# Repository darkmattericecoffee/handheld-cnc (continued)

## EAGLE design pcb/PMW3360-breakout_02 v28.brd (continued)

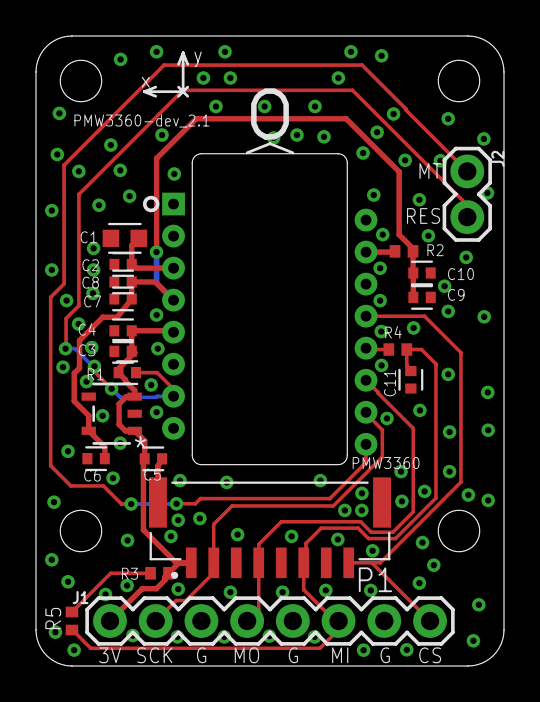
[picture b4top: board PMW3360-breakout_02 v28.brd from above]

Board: 2 copper layers, 26.0 x 35.0 mm, 21 parts (0 on the bottom side), 13 nets.

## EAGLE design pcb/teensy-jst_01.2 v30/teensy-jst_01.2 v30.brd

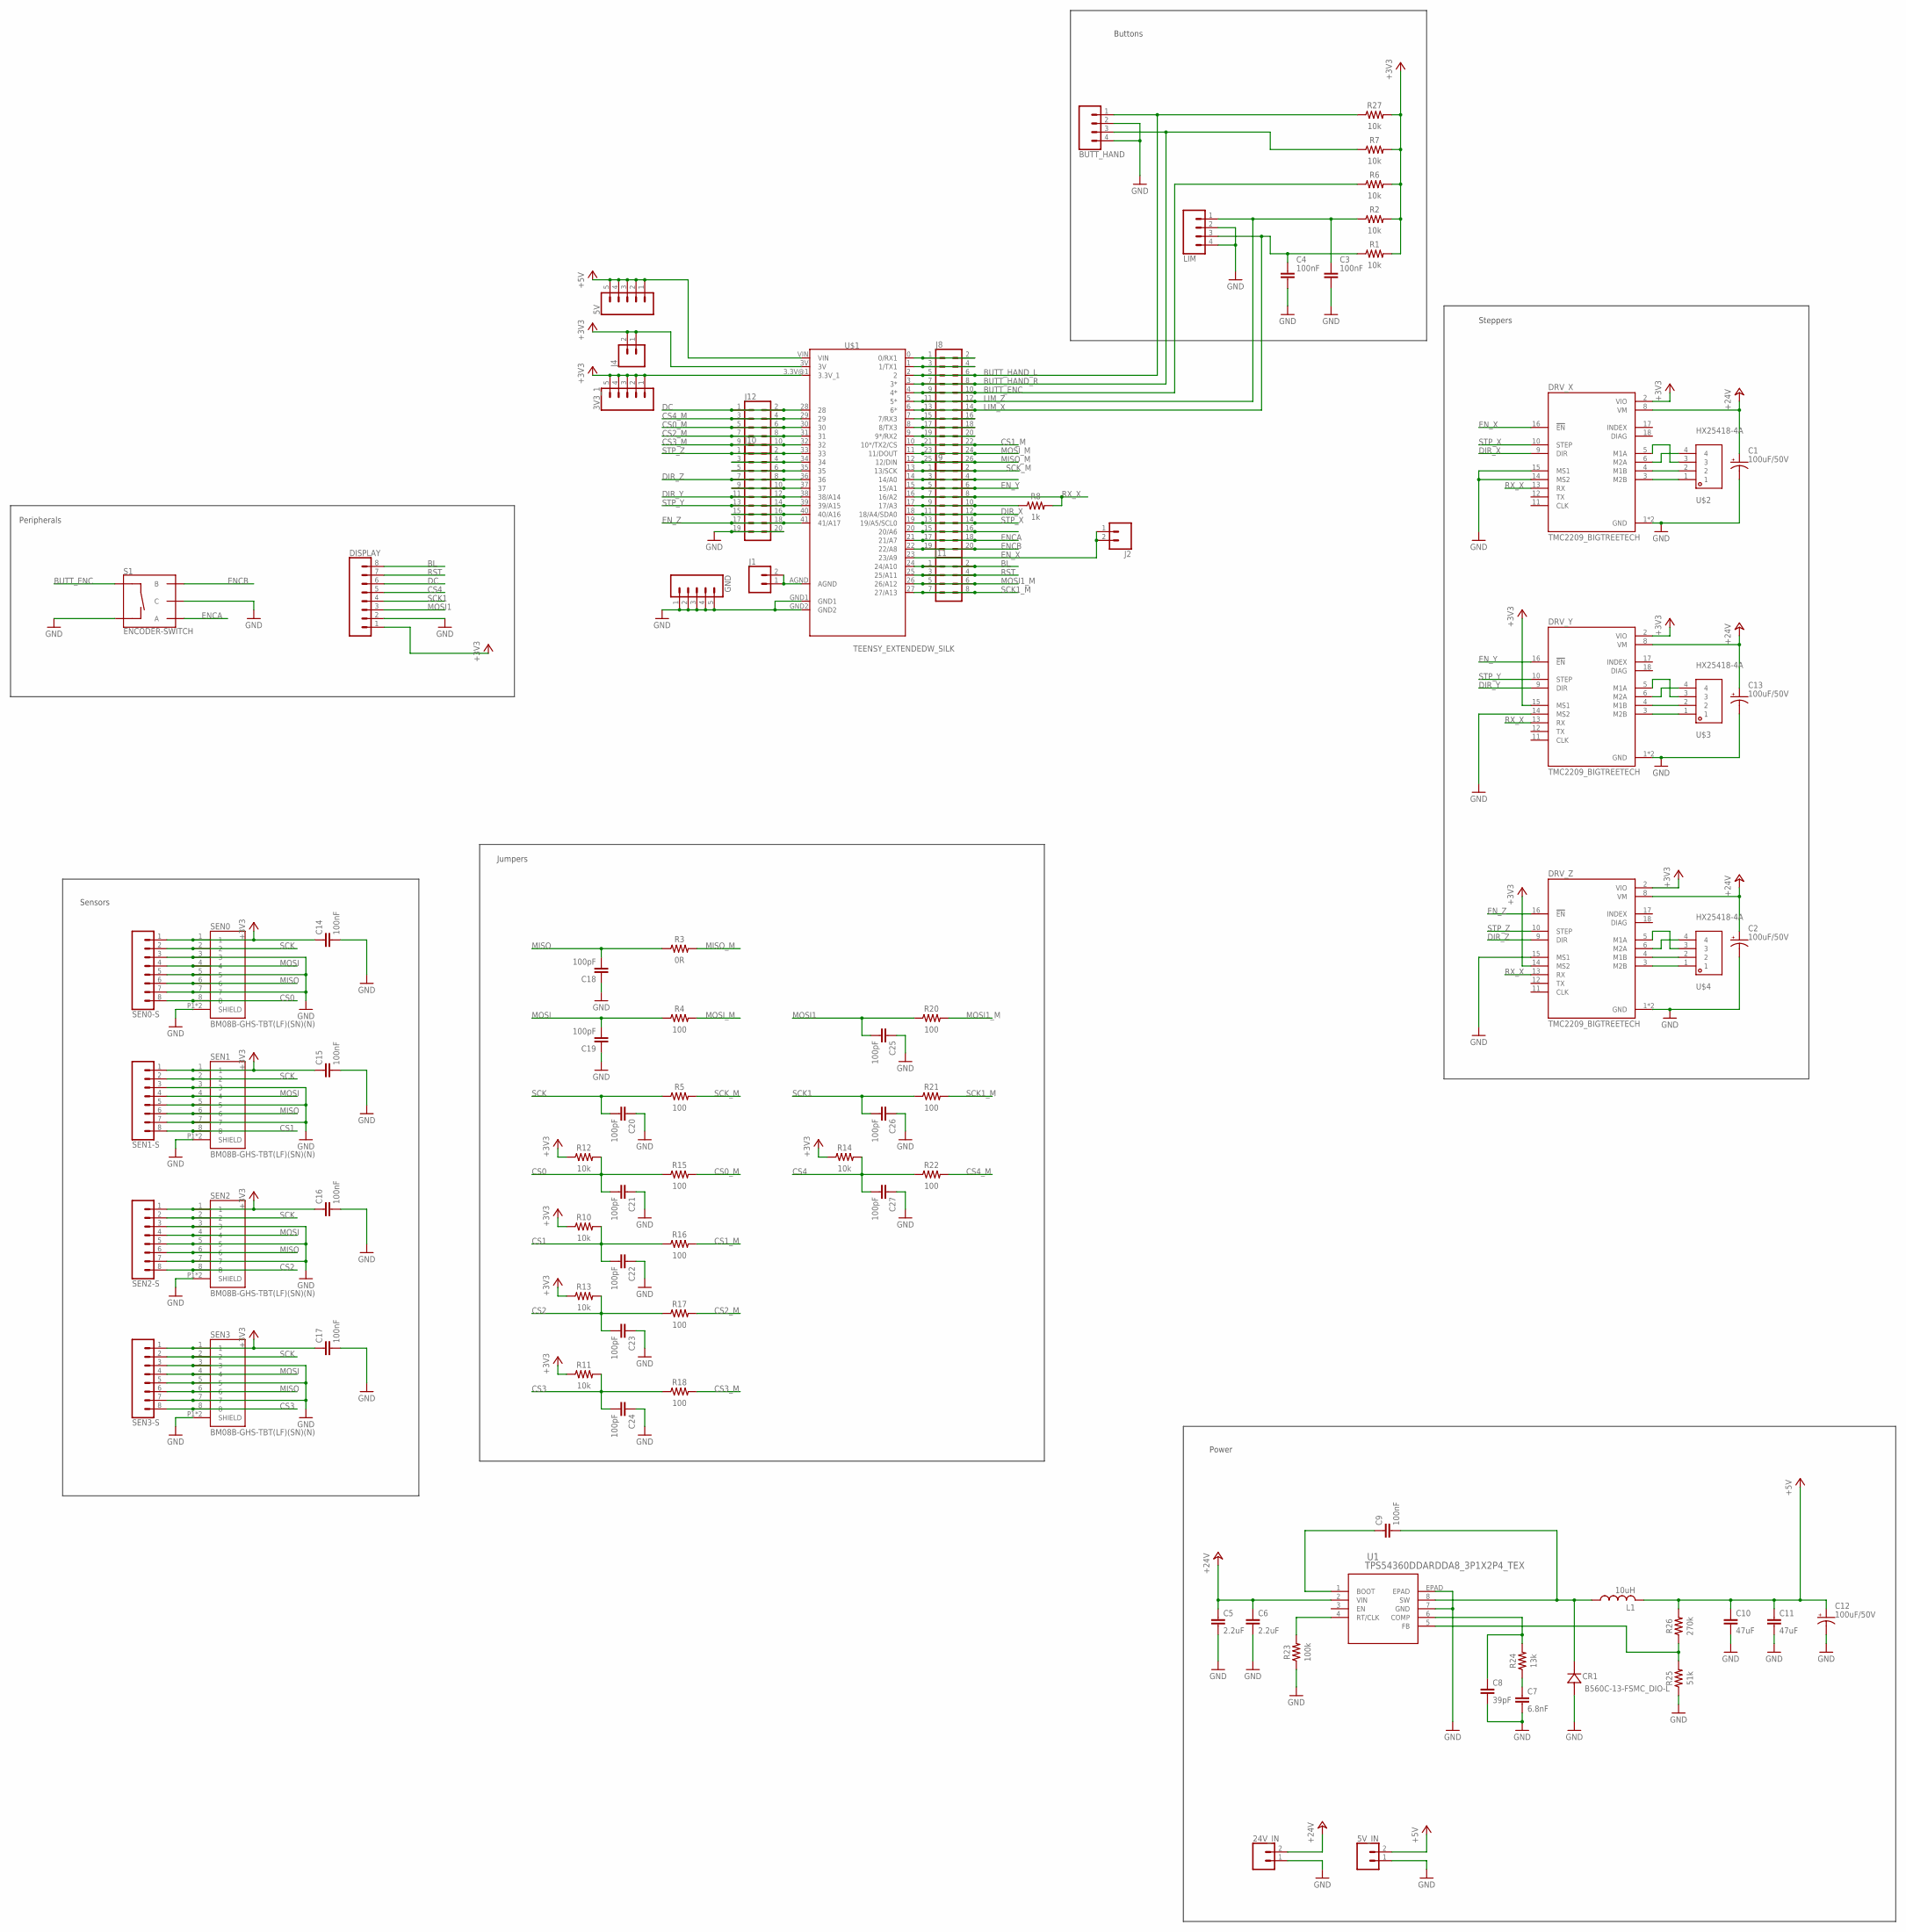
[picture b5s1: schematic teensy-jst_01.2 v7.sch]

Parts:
3V3_1, 5V: CONN_05PTH; 1X05
5V_IN, 24V_IN: CONN_025MM; SCREWTERMINAL-5MM-2
BUTT_HAND: CONN_041X04_NO_SILK; 1X04_NO_SILK
C1, C2, C12, C13: 100uF/50V; PANASONIC_D
C3, C4: 100nF; C0603
C5, C6: 2.2uF; C0603
C7: 6.8nF; C0402
C8: 39pF; C0402
C9, C14, C15, C16, C17: 100nF; C0402
C10, C11: 47uF; C0603
C18, C19, C20, C21, C23, C24, C25, C26, C27: 100pF; C0402K
C22: 100pF; C0402
CR1: B560C-13-FSMC_DIO-L; SMC_DIO-L
DISPLAY: CONN_08"; 1X08
DRV_X: TMC2209_BIGTREETECH; MODULE_TMC2209_BIGTREETECH
DRV_Y: TMC2209_BIGTREETECH; MODULE_TMC2209_BIGTREETECH
DRV_Z: TMC2209_BIGTREETECH; MODULE_TMC2209_BIGTREETECH
GND: CONN_05PTH; 1X05
J1, J2, J4: CONN_02; 1X02
J8: CONN_13X22X13; 2X13
J9, J10: CONN_10X2; 2X10
J11: CONN_04X2; 2X4
J12: CONN_05X2PTH; 2X5
L1: 10uH; MWSA0503S-100MT
LIM: CONN_041X04_NO_SILK; 1X04_NO_SILK
R1, R2, R6, R7, R10, R11, R12, R13, R14, R27: 10k; RESC1608X60
R3: 0R; RESC1608X60
R4, R5, R15, R16, R17, R18, R20, R21, R22: 100; RESC1608X60
R8: 1k; RESC1608X60
R23: 100k; RESC1005X40
R24: 13k; RESC1005X40
R25: 51k; RESC1005X40
R26: 270k; RESC1005X40
S1: ENCODER-SWITCH; ROTARY_ENC_PLAIN
SEN0, SEN1, SEN2, SEN3: BM08B-GHS-TBT(LF)(SN)(N); JST_BM08B-GHS-TBT(LF)(SN)(N)
SEN0-S, SEN1-S, SEN2-S, SEN3-S: CONN_08"; 1X08
U1: TPS54360DDARDDA8_3P1X2P4_TEX; DDA8_3P1X2P4_TEX
U$1: TEENSY_EXTENDEDW_SILK; TEENSY_EXTENDED
U$2, U$3, U$4: HX25418-4A

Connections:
+3V3: 3V3_1.1, 3V3_1.2, 3V3_1.3, 3V3_1.4, 3V3_1.5, C14.1, C15.1, C16.1, C17.1, DISPLAY.1, DRV_X.2 (VIO), DRV_Y.2 (VIO), DRV_Y.15 (MS1), DRV_Z.2 (VIO), DRV_Z.14 (MS2), J4.1, J4.2, R1.2, R2.2, R6.2, R7.2, R10.1, R11.1, R12.1, R13.1, R14.1, R27.2, SEN0.1, SEN0-S.1, SEN1.1, SEN1-S.1, SEN2.1, SEN2-S.1, SEN3.1, SEN3-S.1, U$1.3.3V@1 (3.3V_1), U$1.3V
+5V: 5V.1, 5V.2, 5V.3, 5V.4, 5V.5, 5V_IN.2, C10.1, C11.1, C12.+, L1.2, R26.2, U$1.VIN
+24V: 24V_IN.2, C1.+, C2.+, C5.1, C6.1, C13.+, DRV_X.8 (VM), DRV_Y.8 (VM), DRV_Z.8 (VM), U1.2 (VIN)
BL: DISPLAY.8, J11.1, J11.2, U$1.24 (24/A10)
BUTT_ENC: J8.9, J8.10, R6.1, S1.SW+, U$1.4 (4*)
BUTT_HAND_L: BUTT_HAND.1, J8.5, J8.6, R27.1, U$1.2
BUTT_HAND_R: BUTT_HAND.3, J8.7, J8.8, R7.1, U$1.3 (3*)
CS0: C21.2, R12.2, R15.1, SEN0.8, SEN0-S.8
CS0_M: J12.5, J12.6, R15.2, U$1.30
CS1: C22.2, R10.2, R16.1, SEN1.8, SEN1-S.8
CS1_M: J8.21, J8.22, R16.2, U$1.10 (10*/TX2/CS)
CS2: C23.2, R13.2, R17.1, SEN2.8, SEN2-S.8
CS2_M: J12.7, J12.8, R17.2, U$1.31
CS3: C24.2, R11.2, R18.1, SEN3.8, SEN3-S.8
CS3_M: J12.9, J12.10, R18.2, U$1.32
CS4: C27.2, DISPLAY.5, R14.2, R22.1
CS4_M: J12.3, J12.4, R22.2, U$1.29
DC: DISPLAY.6, J12.1, J12.2, U$1.28
DIR_X: DRV_X.9 (DIR), J9.11, J9.12, U$1.18 (18/A4/SDA0)
DIR_Y: DRV_Y.9 (DIR), J10.11, J10.12, U$1.38 (38/A14)
DIR_Z: DRV_Z.9 (DIR), J10.7, J10.8, U$1.36
ENCA: J9.17, J9.18, S1.A, U$1.21 (21/A7)
ENCB: J9.19, J9.20, S1.B, U$1.22 (22/A8)
EN_X: DRV_X.16 (!EN), J2.1, J2.2, U$1.23 (23/A9)
EN_Y: DRV_Y.16 (!EN), J9.5, J9.6, U$1.15 (15/A1)
EN_Z: DRV_Z.16 (!EN), J10.17, J10.18, U$1.41 (41/A17)
GND: 5V_IN.1, 24V_IN.1, BUTT_HAND.2, BUTT_HAND.4, C1.-, C2.-, C3.2, C4.2, C5.2, C6.2, C7.2, C8.2, C10.2, C11.2, C12.-, C13.-, C14.2, C15.2, C16.2, C17.2, C18.1, C19.1, C20.1, C21.1, C22.1, C23.1, C24.1, C25.1, C26.1, C27.1, CR1.2, DISPLAY.2, DRV_X.1 (GND), DRV_X.7 (GND), DRV_X.14 (MS2), DRV_X.15 (MS1), DRV_Y.1 (GND), DRV_Y.7 (GND), DRV_Y.14 (MS2), DRV_Z.1 (GND), DRV_Z.7 (GND), DRV_Z.15 (MS1), GND.1, GND.2, GND.3, GND.4, GND.5, J10.19, J10.20, LIM.2, LIM.4, R23.1, R25.1, S1.C, S1.SW-, SEN0.3, SEN0.5, SEN0.7, SEN0.P1 (SHIELD), SEN0.P2 (SHIELD), SEN0-S.3, SEN0-S.5, SEN0-S.7, SEN1.3, SEN1.5, SEN1.7, SEN1.P1 (SHIELD), SEN1.P2 (SHIELD), SEN1-S.3, SEN1-S.5, SEN1-S.7, SEN2.3, SEN2.5, SEN2.7, SEN2.P1 (SHIELD), SEN2.P2 (SHIELD), SEN2-S.3, SEN2-S.5, SEN2-S.7, SEN3.3, SEN3.5, SEN3.7, SEN3.P1 (SHIELD), SEN3.P2 (SHIELD), SEN3-S.3, SEN3-S.5, SEN3-S.7, U1.7 (GND), U1.EPAD, U$1.GND1, U$1.GND2
LIM_X: C4.1, J8.13, J8.14, LIM.3, R1.1, U$1.6 (6*)
LIM_Z: C3.1, J8.11, J8.12, LIM.1, R2.1, U$1.5 (5*)
MISO: C18.2, R3.1, SEN0.6, SEN0-S.6, SEN1.6, SEN1-S.6, SEN2.6, SEN2-S.6, SEN3.6, SEN3-S.6
MISO1: J8.3, J8.4, U$1.1 (1/TX1)
MISO_M: J8.25, J8.26, R3.2, U$1.12 (12/DIN)
MOSI: C19.2, R4.1, SEN0.4, SEN0-S.4, SEN1.4, SEN1-S.4, SEN2.4, SEN2-S.4, SEN3.4, SEN3-S.4
MOSI1: C25.2, DISPLAY.3, R20.1
MOSI1_M: J11.5, J11.6, R20.2, U$1.26 (26/A12)
MOSI_M: J8.23, J8.24, R4.2, U$1.11 (11/DOUT)
MS1_Z: J10.9, J10.10, U$1.37
unnamed: J10.15, J10.16, U$1.40 (40/A16)
unnamed: J9.3, J9.4, U$1.14 (14/A0)
unnamed: J1.1, J1.2, U$1.AGND
unnamed: R23.2, U1.4 (RT/CLK)
unnamed: J8.15, J8.16, U$1.7 (7/RX3)
unnamed: C7.1, R24.1
unnamed: DRV_Z.6 (M2A), U$4.4
unnamed: C8.1, R24.2, U1.6 (COMP)
unnamed: DRV_Z.5 (M1A), U$4.3
unnamed: DRV_X.6 (M2A), U$2.4
unnamed: DRV_X.5 (M1A), U$2.3
unnamed: R25.2, R26.1, U1.5 (FB)
unnamed: DRV_Z.4 (M1B), U$4.2
unnamed: DRV_Z.3 (M2B), U$4.1
unnamed: DRV_Y.4 (M1B), U$3.2
unnamed: DRV_X.4 (M1B), U$2.2
unnamed: DRV_X.3 (M2B), U$2.1
unnamed: J9.15, J9.16, U$1.20 (20/A6)
unnamed: J9.9, J9.10, R8.1, U$1.17 (17/A3)
unnamed: DRV_Y.3 (M2B), U$3.1
unnamed: C9.2, CR1.1, L1.1, U1.8 (SW)
unnamed: C9.1, U1.1 (BOOT)
unnamed: J8.17, J8.18, U$1.8 (8/TX3)
unnamed: DRV_Y.6 (M2A), U$3.4
unnamed: J8.1, J8.2, U$1.0 (0/RX1)
unnamed: DRV_Y.5 (M1A), U$3.3
unnamed: J8.19, J8.20, U$1.9 (9*/RX2)
unnamed: J10.5, J10.6, U$1.35
RST: DISPLAY.7, J11.3, J11.4, U$1.25 (25/A11)
RX_X: DRV_X.13 (RX), DRV_Y.13 (RX), DRV_Z.13 (RX), J9.7, J9.8, R8.2, U$1.16 (16/A2)
RX_Z: J10.3, J10.4, U$1.34
SCK: C20.2, R5.1, SEN0.2, SEN0-S.2, SEN1.2, SEN1-S.2, SEN2.2, SEN2-S.2, SEN3.2, SEN3-S.2
SCK1: C26.2, DISPLAY.4, R21.1
SCK1_M: J11.7, J11.8, R21.2, U$1.27 (27/A13)
SCK_M: J9.1, J9.2, R5.2, U$1.13 (13/SCK)
STP_X: DRV_X.10 (STEP), J9.13, J9.14, U$1.19 (19/A5/SCL0)
STP_Y: DRV_Y.10 (STEP), J10.13, J10.14, U$1.39 (39/A15)
STP_Z: DRV_Z.10 (STEP), J10.1, J10.2, U$1.33

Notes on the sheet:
Jumpers
Peripherals
Steppers
Sensors
Power
Buttons

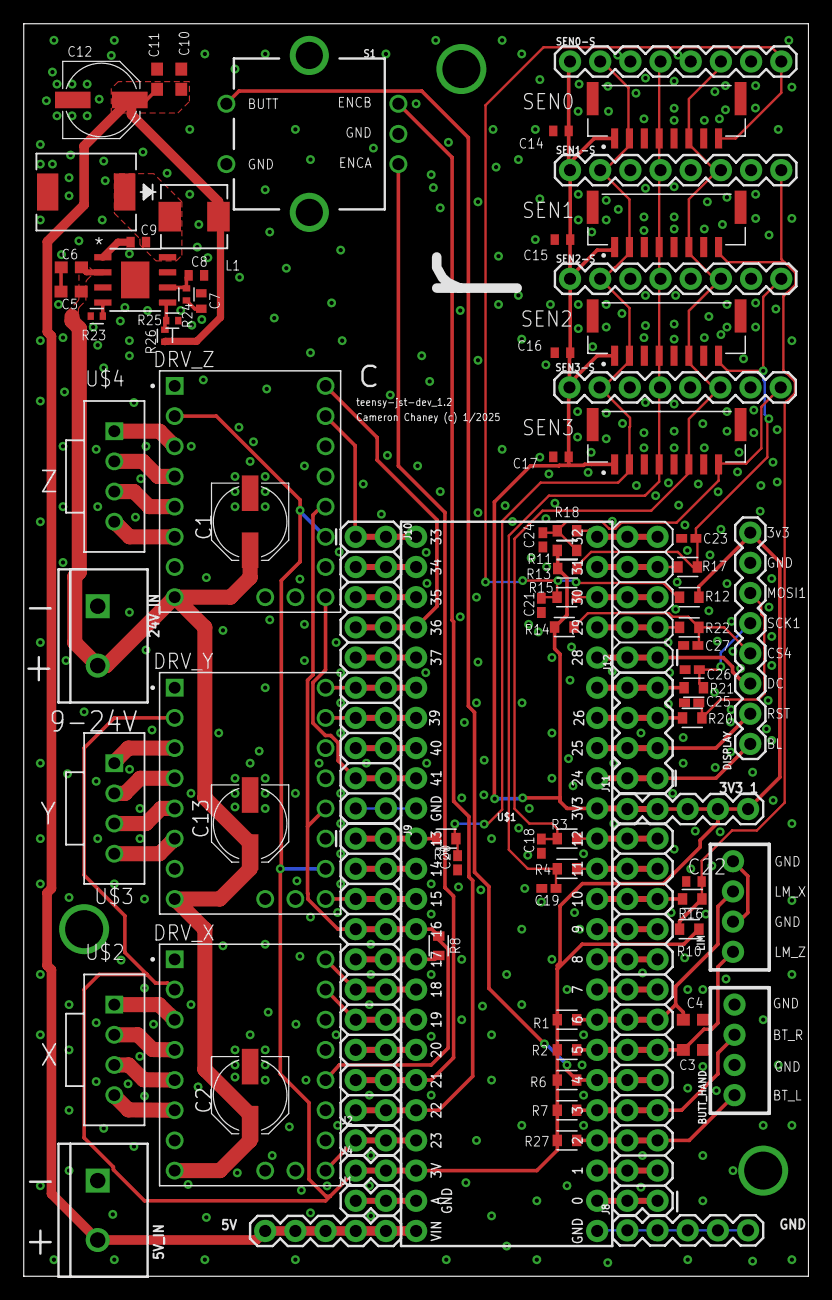
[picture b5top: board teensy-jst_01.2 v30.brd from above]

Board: 2 copper layers, 66.0 x 105.4 mm, 87 parts (0 on the bottom side), 75 nets.

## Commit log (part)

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2023-01-31 adding mouse test code
2023-02-04 adding error propagation function
2023-02-15 progress on mouse sensing
2023-02-15 adding datasheets
2023-02-23 code for ADNS-2610 coordinate sensing
2023-02-24 Add files via upload
    Code for the stepper motor.
2023-02-24 moved step.ino to new location
2023-02-27 Testing mouse
2023-03-09 sensor frame CAD updates
2023-03-09 Hans code
2023-03-14 improving sensing code
    and modifying library
2023-03-14 moving CAD
2023-03-19 calibration done
2023-03-20 body position finding script
    untested
2023-03-20 added simulator and process, deleted obsolete process2.m
2023-03-21 stepper
2023-03-23 render weee
2023-04-06 getting rigid body position and orientation
2023-04-06 created mainCode file
2023-04-16 Testing with teensy
2023-04-16 CAD dev v4
2023-04-16 new positin and vel
2023-04-16 new new
2023-04-16 fixed syntax issues
2023-04-17 mm units now
2023-04-17 control with speed from lib
2023-04-17 Sensor dynamics coded with rect setup
2023-04-19 protoboard dev
2023-04-19 new mainCode for 3 sensors
2023-04-19 stepper speed
2023-04-19 adding button code
2023-04-20 working limit switch code finished
2023-04-21 reordering everything and adding machine x zero
2023-04-21 Revert "moving zero x to one function"
    This reverts commit 0fb0d858cbe01024eca7c047ef0202ff6dfb023d.
2023-04-22 increasing acceleration
2023-04-23 adding sine function drawing
2023-04-27 limit switch made for Z
2023-04-28 work with both motors
2023-04-28 Limit switch failsafes
2023-04-30 showcase updates
2023-06-23 wall crashing fixed and line generator
2023-06-23 implemented signed distance for line crossing alg
2023-06-25 dumb dumb forgot the breaks in switch case
2023-06-25 take path following debug back out
2023-06-26 reset functionality working
    simply press x0y0 button
2023-06-27 update goal point every time reset occurs
2023-06-27 speed test files
2023-07-11 doubled speed with 4 microsteps
    Can go to lower microstepping, but it seems to be too choppy for this application.
2023-07-14 gcode test file made
2023-07-14 got SD working and untested gCode parser
2023-07-14 type fix
2023-07-14 init commit
2023-07-14 add switch to design mode toggle
2023-07-14 update gitignore ds store
2023-07-14 fix bug
2023-07-14 organizing
2023-07-14 bug fix
2023-07-14 docu
    check under docu -> cppDeployment.md for info on how to get started
2023-07-14 cleanup
2023-07-15 new designs
2023-07-15 theoretical interpolator
2023-09-27 CAD update
2023-10-19 CAD and debugging stuff
2023-11-07 zig zag working
2023-11-13 cutting development
2023-11-19 bringing main file up to date
2023-11-19 untrack pio files
2023-11-19 deleting CAD
2023-11-19 more robust lowering for cuts
2023-11-24 fixed potentiometer pinout
2023-12-01 more CAD
2023-12-04 updated readme for new CAD
2023-12-05 removing test scripts
2023-12-05 updated CAD readme
2023-12-05 added base.dxf file
2023-12-24 x machine zero functions combined into one
2024-01-17 adding sensor sled for ogen pcb
2024-01-19 updating CAD for ogen and electrical
2024-01-25 deleting unecessary sleds
2024-01-29 calibration development
2024-01-31 adding in eeprom script
2024-02-02 more progress
2024-02-02 removing unnecessary yup bool
2024-02-09 print raw vals
2024-05-03 bringing calibration back to dev
2024-05-03 cleaning up and moving designs to dev
2024-05-07 moderately better, compiles
2024-05-07 fixing some bugs and testing
2024-05-10 eeprom storage working
    Not writing to eeprom yet, you have to manually enter coeffs in the write function and then run that by pressing "c" to initiate in serial
2024-05-10 added serial_commands python example
    It is dual serial, so you'd have to change that but it's some example code for you. Might want to do something like this for eeprom wiriting to make it esasier, but you can also throw it away if you 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
2024-05-12 updating for EEPROM and fixing mistake
    Realized I had a big mistake when updating the format in a recent commit (35caf797bebce27daa01360cafb4d30068f043c5) where I didn't actually apply the calibration coefficients to the sensor outputs. F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
2024-05-14 fixing bugs with array formatting
2024-05-14 outputSerial function
    With test logFile
2024-05-15 add animation for logs and fix tool position bug
2024-05-15 remove the corrected tool position plot
2024-05-15 fixed that dang desiredposition equation
2024-05-15 undo tool position fix
2024-05-31 rewrite zeroing logic
2024-05-31 add back in cutting. works for existing lines and stuff
2024-06-03 maybe it works who knows
2024-06-03 add more logging
2024-06-04 fix a thing
2024-06-04 semi working multipath
2024-06-06 update plotting
2024-06-06 debug central out here
2024-06-10 half diamond with 1 path
2024-06-10 2 path diamond!
2024-06-11 adding filtering todos
2024-06-13 animation code updated
2024-06-13 super fun SPI1 sensor implementation
2024-06-14 fix sin
2024-06-14 integer math and uncommenting motor
2024-06-14 late night wrap up
    sleepy time
2024-06-15 active dt
2024-06-15 opensauce UI
2024-06-16 fix zeroing bug
2024-07-09 Revert "jank design state drift fix"
    This reverts commit eb99a223ee7252543f7dc20b3d2c710897c88279.
2024-07-12 adding circle again
2024-07-19 weird commit for pull request
2024-07-19 moving dev folder to main repo
2024-07-22 taking out cutting var and updating animator
2024-07-24 set thickness with knob
2024-08-01 software yoffset mimicking
2024-08-02 fixing yOffset implementation
    And fixing the output serial of stepper current position to fix int type error
2024-08-02 just changed some filepath stuff and added if name == main idiom
2024-08-02 Started bare bones of gcode parse and processing
2024-08-02 added segment categorization, in function for given gantry orientation, we have a true or false whether we can cut that point
2024-08-03 adding and tuning xy offsets
2024-08-03 Segment dataframe barebones is there -- need to figure out filtering better
2024-08-20 change function titles
    to be more descriptive
2024-09-11 adding in z compatibility for gcode
2024-10-03 path planning algorithm development
2024-10-07 update pins for new pcb
2024-10-07 fixed gcode parser
    not perfect, but can compile now
2024-10-15 4 sensor integration
    fixing other things too such as motor current, calibration technique (with sensorDebug), and serial commands
2024-10-17 some UI dev
    also increasing z speed, fixing handle buttons, and removing SETTING_THICKNESS
2024-10-18 updating screen library
2024-10-23 adding code from a previous commit
2024-10-23 adding arrows to the plotting function
2024-10-28 plot circle of clusters as well
2024-10-29 github publish dev
2024-10-29 rename to lowercase
2024-10-29 adding to readme
2024-10-29 updating readme and moving files
2024-10-29 adding license
2024-11-05 deleting more unnecessary stuff
2024-11-07 update readme and license md
2024-11-18 new function for kmeans
2024-12-12 splitting up main.cpp into multiple files
2024-12-12 deleting extra main.cpp
2024-12-18 make haul
2024-12-20 reverted button press boolean
    Combining them made it so that the buttons didn't have to be pressed
2024-12-24 found z bug...
    When copying code from stepper X to stepper Z in the driver setup, I forgot to change the TPWMTHRS to Z...
2024-12-24 fixing z skip and more conservative speeds
2025-01-14 gcode parser
2025-01-14 semi working scrolling file display
2025-01-15 horizontal scrolling for file list
2025-01-16 refactor to clean up main
2025-01-20 fixing path generation from gcode
2025-01-20 hole handling overhaul
2025-01-22 debugging stuff
2025-01-22 new cad uploaded
2025-01-22 fixed bug between hole and normal feature I think
    Just changed the advance function from a bool to a void...
2025-01-23 added 3DP version of UIPanel
2025-02-03 config changed for new PCB
2025-02-09 Rename vacBrush_01.stl to suckBristles.stl
2025-02-11 Rename markerMount_jacobs.stl to penMount_papermate.stl
2025-02-14 cad updates
    adding DW611 and other fixes
2025-02-14 changes for new pcb, and other
    Also fixing minZ bug for drawing, adding a minZ property to the path type
2025-02-15 adding spacer
2025-02-20 adding compatibility with aliexpress display
2025-02-20 moving tool mounts to own folder
2025-02-20 pen mounts for cylindrical routers added
2025-02-26 updating step file assembly
2025-02-26 deleting old step file
2025-02-28 adding fully onboard calibration process
    also new drawMenu function
2025-03-03 adding dewalt config.h option
2025-03-06 adding post processor
2025-03-06 updating manual write eeprom function
2025-03-07 better UI
2025-03-10 removing hard coded direction!
    No more do you have to add in direction manually. That's lame
2025-03-11 removing need for gcode modification
    Also allowing for non-numeric post names, and drill instead of hole
2025-03-18 adding calibration progress bar
    And converting tanf to tan2f for sensor misalignment calculation
2025-03-18 adding mother enclosure
2025-03-27 fixed UI panel and new step
2025-03-27 fixing hole bounds
2025-04-03 turning sd card logging back on
2025-04-04 including firmware version on startup
2025-04-04 renaming PMW3360 folder
2025-04-04 binary datalogging dev
2025-04-05 binary datalogging!
    and some general cleanup, mainly in path-execution
2025-04-10 datalogging progress
2025-04-10 sensor packets are decoding
2025-04-11 including calibration values
    And changing sensor data to floats and int instead of ints and byte
2025-04-17 fixing logging time and adding hover cursor
2025-04-17 speed up zeroing
2025-04-18 adding example logFile
2025-05-12 adding sensor velocity comparison
2025-05-12 chicken head working
2025-05-12 simple arbitrary path tracking working
2025-05-12 adding homing and desPos pointer
2025-05-12 gcode parsing fixed for 3d
2025-05-12 improving logging
    - added firmware version to .ini
    - added motorToCartesian function
    - fileMicros timer
    - more handleserial options
    - fixing design in a folder bug
    - add logFile dir if doesn't exist
2025-05-12 fixing sine square generator
2025-05-15 buttons and guard clauses for path execution
2025-05-17 progress bar
2025-05-19 speed run!
2025-06-20 cable notes
2025-06-20 adding pause and feedrateboost
2025-06-26 updating limit switch pinout
2025-06-26 fixing merge bugs
    `
2025-06-26 removing surface quality indicator
    and adding back state change debug
2025-06-26 adding 3 axis cad
2025-07-08 fixing datalogging for 3 axes
2025-07-08 cleaning up path from decoder
2025-07-10 removing old cad files
2025-07-18 adding image
2025-07-19 fixing faulty sensor filtering
    Wasn't dividing by num_good_calcs! Classic
2025-07-24 updating CAD files
    updating a couple parts for 6mm basePlate, as well as updating readme
2025-07-24 updating springmount and baseplate for 6mm
2025-07-30 deeper countersinks for baseplate
2025-07-31 Update README.md for 2x baseStage parts
2025-08-10 adding beltsShim
2025-08-12 PCB design files
2025-08-16 adding sensorJig
2025-08-18 specify stranded wires for sensor cables
2025-08-21 fixing slow retract
2025-08-21 plunge and retract speeds fixed
2025-08-26 fixing speed update after plunge
2025-09-04 doesn't need M800 anymore
2025-09-13 added newer fdm parts
2025-09-26 diamond display fix from opensauce
2025-10-11 fixing nut slots and zKnob
2025-10-15 adding compassLogo example file
2025-10-15 drawing z<0 as 0
2025-10-18 Add path preview functionality and UI enhancements
    - Introduced path preview feature in the UI, allowing users to visualize the path.
    - Added reset functionality for path preview when entering the READY state.
    - Updated display logic to draw path previews conditionally.
    - Implemented functions to clear and store path elements for efficient rendering.
2025-10-18 Implement path preview settings and UI integration
2025-10-18 Add drawIndicator function for UI circle indicators
2025-10-18 Reset path preview on file selection and add debugging output for path bounds. Gcode preview not working yet, generated preview is
2025-10-20 Refactor drawPathPreview function for improved clarity and performance, including enhanced point-in-bounds checks and optimized dot drawing logic.
2025-10-21 Enhance path preview to evenly distribute points along path
2025-10-21 Fix bug with path distribution not unison on small moves
2025-10-21 fix drifting path preview bug in cache coordinates using screen space instead of world space
